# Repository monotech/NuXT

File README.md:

Based on schematics by Sergey Kiselev, with some small changes for combining optimization and board layout efficiency:

http://www.malinov.com/Home/sergeys-projects/isa-fdc-and-uart

http://www.malinov.com/Home/sergeys-projects/xt-cf-lite

http://www.malinov.com/Home/sergeys-projects/isa-supervga

https://github.com/skiselev/micro_8088

https://github.com/skiselev/isa8_backplane

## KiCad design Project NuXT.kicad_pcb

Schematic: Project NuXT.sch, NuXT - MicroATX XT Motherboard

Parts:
C1, C2, C3, C4, C5, C6, C9, C10, C12, C13, C15, C16, C17, C19, C31, C33, C36, C40, C46, C47, C48, C49, C50, C51, C52, C58, C59, C60, C63, C64, C65, C66, C67, C68, C70, C71, C72, C73, C74, C76, C77, C78, C85, C86: 100nF; C_Disc_D4.3mm_W1.9mm_P5.00mm
C8, C20, C21, C23, C24, C25, C26, C27, C28, C29, C30, C35, C56, C57, C61, C62, C69, C75, C79, C80, C81: 10uF; C_Disc_D4.3mm_W1.9mm_P5.00mm
C11, C38, C41, C42, C43, C44, C45, C54, C55, C87: 47pF; C_Disc_D4.3mm_W1.9mm_P5.00mm
C14: 5-30pF; C_Disc_D4.3mm_W1.9mm_P5.00mm
C18, C82, C83: 22pF; C_Disc_D4.3mm_W1.9mm_P5.00mm
C22: 10nF; C_Disc_D4.3mm_W1.9mm_P5.00mm
C34: 1uF; C_Disc_D4.3mm_W1.9mm_P5.00mm
C37: 100pF; C_Disc_D4.3mm_W1.9mm_P5.00mm
C39: 470pF; C_Disc_D4.3mm_W1.9mm_P5.00mm
C53: 1nF; C_Disc_D4.3mm_W1.9mm_P5.00mm
C84: 4.7nF; C_Disc_D4.3mm_W1.9mm_P5.00mm
D1, D4, D5: 1N4148; D_DO-34_SOD68_P7.62mm_Horizontal
D3: Bus Activity; LED_D3.0mm
D6: CF Activity; LED_D3.0mm
D7: 5VSB; LED_D3.0mm
D8: +5V; LED_D3.0mm
D9: +12V; LED_D3.0mm
D10: -12V; LED_D3.0mm
D11: -5V; LED_D3.0mm
F1: 1.1A; C_Disc_D4.3mm_W1.9mm_P5.00mm
FB1, FB2, FB3, FB4, FB5, FB6: BEAD; R_Axial_DIN0204_L3.6mm_D1.6mm_P7.62mm_Horizontal
HOLE1, HOLE2, HOLE3, HOLE4, HOLE5, HOLE6: HOLE; MountingHole_4mm_Pad_Via
ISA1, ISA2, ISA3, ISA4: BUSPC_HOST; Conn_Edge_ISA8_Longpads
JP1: UART Config; PinHeader_2x08_P2.54mm_Vertical
L1: 2.7uH; R_Axial_DIN0207_L6.3mm_D2.5mm_P7.62mm_Horizontal
L2, L3: 5.7uH; R_Axial_DIN0207_L6.3mm_D2.5mm_P7.62mm_Horizontal
LOGO1: SYM_Arrow45_Large; Monotech Logo 18mm
LOGO2: SYM_Arrow45_Large; Monotech Logo 92mm
P1: Front Panel; PinHeader_2x05_P2.54mm_Horizontal
P2: Speaker; PinHeader_1x04_P2.54mm_Horizontal
P3: ATX Power; Molex_Mini-Fit_Jr_5569-20A2_2x10_P4.20mm_Horizontal
P4: Floppy; Pin_Header_Straight_2x17_Pitch2.54mm_shrouded
P5: PS/2 Keyboard; Conn_Mini_DIN_6pin
P6: Serial Port; Conn_Dsub_DE9M
P7: VGA Port; DSUB-15-HD_Female_Horizontal_CONNFLY_DS1308
P8: CF_CARD; CF_Slot_3M_N7E50-7516TS0884
Q1: PN2222 EBC; TO-92L_Inline_Wide
R1, R15: 470; R_Axial_DIN0207_L6.3mm_D2.5mm_P7.62mm_Horizontal
R2, R33: 1M; R_Axial_DIN0207_L6.3mm_D2.5mm_P7.62mm_Horizontal
R3, R11, R14, R16, R31: 10K; R_Axial_DIN0207_L6.3mm_D2.5mm_P7.62mm_Horizontal
R4, R5: 47; R_Axial_DIN0207_L6.3mm_D2.5mm_P7.62mm_Horizontal
R6, R7, R8, R12, R13, R18, R29, R30: 1K; R_Axial_DIN0207_L6.3mm_D2.5mm_P7.62mm_Horizontal
R9, R21, R22: 33; R_Axial_DIN0207_L6.3mm_D2.5mm_P7.62mm_Horizontal
R10, R20, R26, R27: 4.7K; R_Axial_DIN0207_L6.3mm_D2.5mm_P7.62mm_Horizontal
R17: 100; R_Axial_DIN0207_L6.3mm_D2.5mm_P7.62mm_Horizontal
R19, R23, R24, R25: 150; R_Axial_DIN0207_L6.3mm_D2.5mm_P7.62mm_Horizontal
R28: 5.6K; R_Axial_DIN0207_L6.3mm_D2.5mm_P7.62mm_Horizontal
R32: 1.5K; R_Axial_DIN0207_L6.3mm_D2.5mm_P7.62mm_Horizontal
RN1: 4.7K; R_Array_SIP9
RN2, RN3, RN6, RN14, RN15: 10K; R_Array_SIP9
RN4, RN5, RN12: 4.7K; R_Array_SIP7
RN13: 1K; R_Array_SIP7
SP1: Speaker; MagneticBuzzer_ProSignal_ABT-410-RC
SW1: System Config; SW_DIP_SPSTx10_Slide_9.78x27.58mm_W7.62mm_P2.54mm
SW2: UMB Config; SW_DIP_SPSTx05_Slide_9.78x14.88mm_W7.62mm_P2.54mm
SW3: ROM Socket Address; SW_DIP_SPSTx04_Slide_9.78x12.34mm_W7.62mm_P2.54mm
SW4: U35 ROM Size; SW_MS-22D18G2
SW5: Power; SW_PUSH_6mm
SW6: Reset; SW_PUSH_6mm
U1: 8088; DIP-40_W15.24mm_Socket
U2: 8087; DIP-40_W15.24mm_Socket
U3: SST39SF010A; DIP-32_W15.24mm_Socket
U4, U5: AS6C4008; SSOP-32_11.305x20.495mm_P1.27mm
U6: FE2010A; PLCC-84_THT-Socket
U7: ATF16V8B; DIP-20_W7.62mm_Socket
U9: PIC12F629; DIP-8_W7.62mm_Socket
U10, U11, U12: 74F573; DIP-20_W7.62mm
U13, U14: 74F245; DIP-20_W7.62mm
U15, U16: 74F244; DIP-20_W7.62mm
U17: 74LS14; DIP-14_W7.62mm
U18: 74LS74; DIP-14_W7.62mm
U19: 7905; TO220-3_Soldertab
U20: TVGA9000i; PQFP-160_28x28mm_P0.65mm_LongPads
U21: 27C256; DIP-28_W15.24mm_Socket
U22, U23, U24, U25: 256Kx4 70ns; DIP-20_W7.62mm_Socket
U26, U36: 74LS688; DIP-20_W7.62mm
U27: 74LS32; DIP-14_W7.62mm
U28: 74LS04; DIP-14_W7.62mm
U29: 82077AA/PC8477; PLCC-68_THT-Socket
U30: 16(C)x50; PLCC-44_THT-Socket
U31: GD75232/75(C)185; DIP-20_W7.62mm
U32, U33: 74LS138; DIP-16_W7.62mm
U35: 28C64B/28C256; DIP-28_W15.24mm_Socket
X1: 28.63636MHz; Crystal_HC49-4H_Vertical
X2: 40MHz; Crystal_HC49-4H_Vertical
X3: 1.8432MHz TTL; Oscillator_DIP-14
X4: 24MHz; Crystal_HC49-4H_Vertical
X5: 1.8432MHz; Crystal_HC49-U_Horizontal_Solderpad

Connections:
/0x2E8: JP1.9, U32.11 (~Y4)
/0x2F8: JP1.13, U32.9 (~Y6)
/0x3E8: JP1.11, U32.10 (~Y5)
/0x3F0: SW1.16, U32.12 (~Y3)
/0x3F8: JP1.15, U32.7 (~Y7)
/5VSB: C29.1, C31.1, C33.1, D4.1 (K), D5.1 (K), D7.2 (A), P3.9 (5VSB), R14.1, R16.1, U17.9, U17.11, U17.13, U17.14 (VCC), U18.1 (~R), U18.10 (~S), U18.13 (~R), U18.14 (VCC)
/12V: C30.1, C73.1, C75.1, D9.2 (A), ISA1.9 (+12V), ISA2.9 (+12V), ISA3.9 (+12V), ISA4.9 (+12V), P3.10 (12V), U31.1 (VDD)
/-5V: C28.2, D11.1 (K), ISA1.5 (-5V), ISA2.5 (-5V), ISA3.5 (-5V), ISA4.5 (-5V), U19.3 (OUT)
/-12V: C24.2, C78.2, C79.2, D10.1 (K), ISA1.7 (-12V), ISA2.7 (-12V), ISA3.7 (-12V), ISA4.7 (-12V), P3.12 (-12V), U19.2 (IN), U31.10 (VSS)
/A0: ISA1.62 (SA0), ISA2.62 (SA0), ISA3.62 (SA0), ISA4.62 (SA0), U3.12 (A0), U4.12 (A0), U5.12 (A0), U10.19 (O0), U20.135 (SA0), U29.7 (A0), U30.31 (A0), U35.10 (A0)
/A1: ISA1.61 (SA1), ISA2.61 (SA1), ISA3.61 (SA1), ISA4.61 (SA1), P8.20 (A0), U3.11 (A1), U4.11 (A1), U5.11 (A1), U10.18 (O1), U20.136 (SA1), U21.10 (A0), U29.8 (A1), U30.30 (A1), U35.9 (A1)
/A2: ISA1.60 (SA2), ISA2.60 (SA2), ISA3.60 (SA2), ISA4.60 (SA2), P8.19 (A1), U3.10 (A2), U4.10 (A2), U5.10 (A2), U10.17 (O2), U20.137 (SA2), U21.9 (A1), U29.10 (A2), U30.29 (A2), U35.8 (A2)
/A3: ISA1.59 (SA3), ISA2.59 (SA3), ISA3.59 (SA3), ISA4.59 (SA3), P8.18 (A2), U3.9 (A3), U4.9 (A3), U5.9 (A3), U10.16 (O3), U20.138 (SA3), U21.8 (A2), U32.3 (C), U35.7 (A3)
/A4: ISA1.58 (SA4), ISA2.58 (SA4), ISA3.58 (SA4), ISA4.58 (SA4), U3.8 (A4), U4.8 (A4), U5.8 (A4), U10.15 (O4), U20.139 (SA4), U21.7 (A3), U27.4, U28.1, U32.2 (B), U35.6 (A4)
/A5: ISA1.57 (SA5), ISA2.57 (SA5), ISA3.57 (SA5), ISA4.57 (SA5), U3.7 (A5), U4.7 (A5), U5.7 (A5), U10.14 (O5), U20.140 (SA5), U21.6 (A4), U26.2 (P0), U32.6 (G1), U35.5 (A5)
/A6: ISA1.56 (SA6), ISA2.56 (SA6), ISA3.56 (SA6), ISA4.56 (SA6), U3.6 (A6), U4.6 (A6), U5.6 (A6), U10.13 (O6), U20.141 (SA6), U21.5 (A5), U26.4 (P1), U33.1 (A), U35.4 (A6)
/A7: ISA1.55 (SA7), ISA2.55 (SA7), ISA3.55 (SA7), ISA4.55 (SA7), R12.1, U3.5 (A7), U4.5 (A7), U5.5 (A7), U10.12 (O7), U20.142 (SA7), U21.4 (A6), U26.6 (P2), U33.2 (B), U35.3 (A7)
/A8: ISA1.54 (SA8), ISA2.54 (SA8), ISA3.54 (SA8), ISA4.54 (SA8), U3.27 (A8), U4.27 (A8), U5.27 (A8), U11.19 (O0), U20.144 (SA8), U21.3 (A7), U26.8 (P3), U32.1 (A), U35.25 (A8)
/A9: ISA1.53 (SA9), ISA2.53 (SA9), ISA3.53 (SA9), ISA4.53 (SA9), U3.26 (A9), U4.26 (A9), U5.26 (A9), U11.18 (O1), U20.145 (SA9), U21.25 (A8), U26.11 (P4), U33.3 (C), U35.24 (A9)
/A10: ISA1.52 (SA10), ISA2.52 (SA10), ISA3.52 (SA10), ISA4.52 (SA10), U3.23 (A10), U4.23 (A10), U5.23 (A10), U11.17 (O2), U20.146 (SA10), U21.24 (A9), U35.21 (A10)
/A11: ISA1.51 (SA11), ISA2.51 (SA11), ISA3.51 (SA11), ISA4.51 (SA11), U3.25 (A11), U4.25 (A11), U5.25 (A11), U11.16 (O3), U20.147 (SA11), U21.21 (A10), U35.23 (A11)
/A12: ISA1.50 (SA12), ISA2.50 (SA12), ISA3.50 (SA12), ISA4.50 (SA12), U3.4 (A12), U4.4 (A12), U5.4 (A12), U11.15 (O4), U20.148 (SA12), U21.23 (A11), U35.2 (A12)
/A13: ISA1.49 (SA13), ISA2.49 (SA13), ISA3.49 (SA13), ISA4.49 (SA13), SW4.5 (B), U3.28 (A13), U4.28 (A13), U5.28 (A13), U11.14 (O5), U20.149 (SA13), U21.2 (A12), U35.26 (A13)
/A14: ISA1.48 (SA14), ISA2.48 (SA14), ISA3.48 (SA14), ISA4.48 (SA14), SW4.2 (B), U3.29 (A14), U4.3 (A14), U5.3 (A14), U11.13 (O6), U20.150 (SA14), U21.26 (A13), U35.1 (A14)
/A15: ISA1.47 (SA15), ISA2.47 (SA15), ISA3.47 (SA15), ISA4.47 (SA15), U3.3 (A15), U4.31 (A15), U5.31 (A15), U7.9 (I8), U11.12 (O7), U20.151 (SA15), U36.5 (R1)
/A16: ISA1.46 (SA16), ISA2.46 (SA16), ISA3.46 (SA16), ISA4.46 (SA16), U4.2 (A16), U5.2 (A16), U7.5 (I4), U12.15 (O4), U20.152 (SA16), U36.3 (R0)
/A17: ISA1.45 (SA17), ISA2.45 (SA17), ISA3.45 (SA17), ISA4.45 (SA17), U4.30 (A17), U5.30 (A17), U7.6 (I5), U12.14 (O5), U20.113 (SA17(LA17)), U36.14 (R5)
/A18: ISA1.44 (SA18), ISA2.44 (SA18), ISA3.44 (SA18), ISA4.44 (SA18), U4.1 (A18), U5.1 (A18), U7.7 (I6), U12.13 (O6), U20.114 (SA18(LA18)), U36.16 (R6)
/A19: ISA1.43 (SA19), ISA2.43 (SA19), ISA3.43 (SA19), ISA4.43 (SA19), U4.22 (~CE), U7.8 (I7), U12.12 (O7), U20.115 (SA19(LA19)), U36.18 (R7)
/AA8: U1.8 (A8), U2.8 (AD8), U6.44 (A8), U11.2 (D0)
/AA9: U1.7 (A9), U2.7 (AD9), U6.45 (A9), U11.3 (D1)
/AA10: U1.6 (A10), U2.6 (AD10), U6.46 (A10), U11.4 (D2)
/AA11: U1.5 (A11), U2.5 (AD11), U6.47 (A11), U11.5 (D3)
/AA12: U1.4 (A12), U2.4 (AD12), U6.48 (A12), U11.6 (D4)
/AA13: U1.3 (A13), U2.3 (AD13), U6.49 (A13), U11.7 (D5)
/AA14: U1.2 (A14), U2.2 (AD14), U6.50 (A14), U11.8 (D6)
/AA15: U1.39 (A15), U2.39 (AD15), U6.51 (A15), U11.9 (D7)
/AA16: U1.38 (A16/S3), U2.38 (A16/S3), U6.52 (A16), U12.6 (D4)
/AA17: U1.37 (A17/S4), U2.37 (A17/S4), U6.53 (A17), U12.7 (D5)
/AA18: U1.36 (A18/S5), U2.36 (A18/S5), U6.54 (A18), U12.8 (D6)
/AA19: U1.35 (A19/S6), U2.35 (A19/S6), U6.55 (A19), U12.9 (D7)
/AD0: U1.16 (AD0), U2.16 (AD0), U3.13 (DQ0), U6.34 (AD0), U10.2 (D0), U13.2 (A1)
/AD1: U1.15 (AD1), U2.15 (AD1), U3.14 (DQ1), U6.35 (AD1), U10.3 (D1), U13.3 (A2)
/AD2: U1.14 (AD2), U2.14 (AD2), U3.15 (DQ2), U6.36 (AD2), U10.4 (D2), U13.4 (A3)
/AD3: U1.13 (AD3), U2.13 (AD3), U3.17 (DQ3), U6.37 (AD3), U10.5 (D3), U13.5 (A4)
/AD4: U1.12 (AD4), U2.12 (AD4), U3.18 (DQ4), U6.38 (AD4), U10.6 (D4), U13.6 (A5)
/AD5: U1.11 (AD5), U2.11 (AD5), U3.19 (DQ5), U6.39 (AD5), U10.7 (D5), U13.7 (A6)
/AD6: U1.10 (AD6), U2.10 (AD6), U3.20 (DQ6), U6.40 (AD6), U10.8 (D6), U13.8 (A7)
/AD7: U1.9 (AD7), U2.9 (AD7), U3.21 (DQ7), U6.41 (AD7), U10.9 (D7), U13.9 (A8)
/AEN: ISA1.42 (AEN), ISA2.42 (AEN), ISA3.42 (AEN), ISA4.42 (AEN), SW1.12, SW1.15, U16.16 (Y2), U20.22 (AEN), U32.4 (~G2A)
/ALE: ISA1.28 (ALE), ISA2.28 (ALE), ISA3.28 (ALE), ISA4.28 (ALE), U15.3 (Y4)
/APNMI: U2.32 (INT), U6.29 (APNMI)
/AT_KBCLK: D1.2 (A), P5.5, RN5.3 (R2), U9.5 (GP2/T0CKI/INT/COUT)
/AT_KBDATA: P5.1, RN5.2 (R1), U9.6 (GP1/CIN-/ICSPCLK)
/AVDD1: C40.1, C56.1, C59.1, L2.2, U20.124 (AVDD1)
/AVDD2: C57.1, C60.1, L3.2, U20.6 (AVDD2), U20.13 (AVDD2)
/B: FB3.1, R25.1, U20.2 (B)
/BLUE: C45.1, FB3.2, P7.3
/CF_DMARQ: P8.43 (~INPACK), R28.1
/CF_IORDY: P8.42 (IORDY), R30.1
/CLK: ISA1.20 (CLK), ISA2.20 (CLK), ISA3.20 (CLK), ISA4.20 (CLK), R5.1
/CLK88: U1.19 (CLK), U2.19 (CLK), U6.19 (CLOCK), U15.8 (A4)
/CS_RomSocket: U35.20 (CS), U36.19 (P=R)
/CTS: P6.8, U31.7 (RA4)
/D0: ISA1.40 (SD0), ISA2.40 (SD0), ISA3.40 (SD0), ISA4.40 (SD0), P8.21 (D0), RN2.2 (R1), U13.18 (B1), U14.2 (A1), U20.25 (SD0), U29.11 (DB0), U30.2 (D0), U35.11 (D0)
/D1: ISA1.39 (SD1), ISA2.39 (SD1), ISA3.39 (SD1), ISA4.39 (SD1), P8.22 (D1), RN2.3 (R2), U13.17 (B2), U14.3 (A2), U20.26 (SD1), U29.13 (DB1), U30.3 (D1), U35.12 (D1)
/D2: ISA1.38 (SD2), ISA2.38 (SD2), ISA3.38 (SD2), ISA4.38 (SD2), P8.23 (D2), RN2.4 (R3), U13.16 (B3), U14.4 (A3), U20.27 (SD2), U29.14 (DB2), U30.4 (D2), U35.13 (D2)
/D3: ISA1.37 (SD3), ISA2.37 (SD3), ISA3.37 (SD3), ISA4.37 (SD3), P8.2 (D3), RN2.5 (R4), U13.15 (B4), U14.5 (A4), U20.28 (SD3), U29.15 (DB3), U30.5 (D3), U35.15 (D3)
/D4: ISA1.36 (SD4), ISA2.36 (SD4), ISA3.36 (SD4), ISA4.36 (SD4), P8.3 (D4), RN2.6 (R5), U13.14 (B5), U14.6 (A5), U20.29 (SD4), U29.17 (DB4), U30.6 (D4), U35.16 (D4)
/D5: ISA1.35 (SD5), ISA2.35 (SD5), ISA3.35 (SD5), ISA4.35 (SD5), P8.4 (D5), RN2.7 (R6), U13.13 (B6), U14.7 (A6), U20.30 (SD5), U29.19 (DB5), U30.7 (D5), U35.17 (D5)
/D6: ISA1.34 (SD6), ISA2.34 (SD6), ISA3.34 (SD6), ISA4.34 (SD6), P8.5 (D6), RN2.8 (R7), U13.12 (B7), U14.8 (A7), U20.31 (SD6), U29.20 (DB6), U30.8 (D6), U35.18 (D6)
/D7: ISA1.33 (SD7), ISA2.33 (SD7), ISA3.33 (SD7), ISA4.33 (SD7), P8.6 (D7), RN2.9 (R8), U13.11 (B8), U14.9 (A8), U20.32 (SD7), U29.22 (DB7), U30.9 (D7), U35.19 (D7)
/DCD: P6.1, U31.2 (RA1)
/DENSL: P4.2, U29.49 (DENSEL)
/DIR: U6.72 (DTR), U13.1 (DIR)
/DRQ1: ISA1.18 (DRQ1), ISA2.18 (DRQ1), ISA3.18 (DRQ1), ISA4.18 (DRQ1), U6.58 (DRQ1)
/DRQ2: ISA1.6 (DRQ2), ISA2.6 (DRQ2), ISA3.6 (DRQ2), ISA4.6 (DRQ2), U6.57 (DRQ2), U29.24 (DRQ)
/DRQ3: ISA1.16 (DRQ3), ISA2.16 (DRQ3), ISA3.16 (DRQ3), ISA4.16 (DRQ3), U6.56 (DRQ3)
/DSA: P4.14, U29.58 (DS0)
/DSB: P4.12, U29.62 (DS1)
/DSKCG: P4.34, RN13.6 (R5), U29.31 (DSKCHG)
/DSR: P6.6, U31.3 (RA2)
/DTR: P6.4, U31.8 (DY3)
/E0_PASS: RN15.4 (R3), SW1.3, U9.4 (GP3/~MCLR~/Vpp)
/EN_RomSocket: RN6.2 (R1), SW1.9, U36.1 (G)
/EOP: U6.59 (EOP), U15.4 (A2)
/FloppyDIR: P4.18, U29.56 (DIR)
/G: FB2.1, R24.1, U20.3 (G)
/GREEN: C44.1, FB2.2, P7.2
/HDD_LED_Ext: P1.3, U28.10
/HDSEL: P4.32, U29.51 (HDSEL)
/HSYNC: FB5.2, U20.48 (HSYNC)
/INDEX: P4.8, RN13.2 (R1), U29.26 (INDX)
/INT: U1.18 (INTR), U6.10 (INT)
/IORDY: ISA1.41 (IO_READY), ISA2.41 (IO_READY), ISA3.41 (IO_READY), ISA4.41 (IO_READY), U6.28 (IORDY), U20.157 (IOCHRDY)
/IRQ2: ISA1.4 (IRQ2), ISA2.4 (IRQ2), ISA3.4 (IRQ2), ISA4.4 (IRQ2), U6.76 (IRQ2)
/IRQ3: ISA1.25 (IRQ3), ISA2.25 (IRQ3), ISA3.25 (IRQ3), ISA4.25 (IRQ3), JP1.1, U6.77 (IRQ3)
/IRQ4: ISA1.24 (IRQ4), ISA2.24 (IRQ4), ISA3.24 (IRQ4), ISA4.24 (IRQ4), JP1.3, U6.78 (IRQ4)
/IRQ5: ISA1.23 (IRQ5), ISA2.23 (IRQ5), ISA3.23 (IRQ5), ISA4.23 (IRQ5), JP1.5, U6.79 (IRQ5)
/IRQ6: ISA1.22 (IRQ6), ISA2.22 (IRQ6), ISA3.22 (IRQ6), ISA4.22 (IRQ6), U6.80 (IRQ6), U29.23 (INT)
/IRQ7: ISA1.21 (IRQ7), ISA2.21 (IRQ7), ISA3.21 (IRQ7), ISA4.21 (IRQ7), JP1.7, U6.81 (IRQ7)
/KBCLK: RN5.4 (R3), U6.25 (KBCLK), U9.2 (GP5/T1CKI/OSC1/CLKIN)
/KBDATA: RN5.5 (R4), U6.26 (KBDA), U9.3 (GP4/~T1G~/OSC2/CLKOUT)
/KBD_VCC: F1.1, P5.4
/LE: U6.70 (ALE), U10.11 (LE), U11.11 (LE), U12.11 (LE)
/MAA0: U20.52 (MAA0), U22.6 (A0), U24.6 (A0)
/MAA1: U20.53 (MAA1), U22.7 (A1), U24.7 (A1)
/MAA2: U20.54 (MAA2), U22.8 (A2), U24.8 (A2)
/MAA3: U20.55 (MAA3), U22.9 (A3), U24.9 (A3)
/MAA4: U20.56 (MAA4), U22.11 (A4), U24.11 (A4)
/MAA5: U20.57 (MAA5), U22.12 (A5), U24.12 (A5)
/MAA6: U20.59 (MAA6), U22.13 (A6), U24.13 (A6)
/MAA7: U20.60 (MAA7), U22.14 (A7), U24.14 (A7)
/MAA8: U20.61 (MAA8), U22.15 (A8), U24.15 (A8)
/MAB0: U20.73 (MAB0), U23.6 (A0), U25.6 (A0)
/MAB1: U20.74 (MAB1), U23.7 (A1), U25.7 (A1)
/MAB2: U20.75 (MAB2), U23.8 (A2), U25.8 (A2)
/MAB3: U20.76 (MAB3), U23.9 (A3), U25.9 (A3)
/MAB4: U20.77 (MAB4), U23.11 (A4), U25.11 (A4)
/MAB5: U20.78 (MAB5), U23.12 (A5), U25.12 (A5)
/MAB6: U20.82 (MAB6), U23.13 (A6), U25.13 (A6)
/MAB7: U20.83 (MAB7), U23.14 (A7), U25.14 (A7)
/MAB8: U20.84 (MAB8), U23.15 (A8), U25.15 (A8)
/MD0: U4.13 (DQ0), U5.13 (DQ0), U14.18 (B1)
/MD1: U4.14 (DQ1), U5.14 (DQ1), U14.17 (B2)
/MD2: U4.15 (DQ2), U5.15 (DQ2), U14.16 (B3)
/MD3: U4.17 (DQ3), U5.17 (DQ3), U14.15 (B4)
/MD4: U4.18 (DQ4), U5.18 (DQ4), U14.14 (B5)
/MD5: U4.19 (DQ5), U5.19 (DQ5), U14.13 (B6)
/MD6: U4.20 (DQ6), U5.20 (DQ6), U14.12 (B7)
/MD7: U4.21 (DQ7), U5.21 (DQ7), U14.11 (B8)
/MEA: P4.10, U29.57 (ME0)
/MEB: P4.16, U29.61 (ME1)
/MONITOR: FB4.2, R26.1, U20.46 (MONITOR)
/NMI: U1.17 (NMI), U6.31 (NMI)
/OSC: U6.20 (OSC), U15.2 (A1)
/OSCDRV: ISA1.30 (OSC), ISA2.30 (OSC), ISA3.30 (OSC), ISA4.30 (OSC), R4.1, U20.98 (ROMCLK)
/PWR_SW: P1.6, R14.2, R15.2, SW5.2
/QS0: U1.25 (QS0), U2.25 (QS0)
/QS1: U1.24 (QS1), U2.24 (QS1)
/R: FB1.1, R23.1, U20.4 (R)
/RDATA: P4.30, RN13.5 (R4), U29.41 (RDDATA)
/READY: U1.22 (READY), U2.22 (READY), U6.17 (READY)
/RED: C43.1, FB1.2, P7.1
/RESET: U1.21 (RESET), U2.21 (RESET), U6.18 (RESET), U16.2 (A1)
/RI: P6.9, U31.9 (RA5)
/RMD0: U20.43 (RMD0), U21.11 (DQ0)
/RMD1: SW1.14, U20.39 (RMD1), U21.12 (DQ1)
/RMD2: U20.38 (RMD2), U21.13 (DQ2)
/RMD3: U20.37 (RMD3), U21.15 (DQ3)
/RMD4: RN12.3 (R2), U20.36 (RMD4), U21.16 (DQ4)
/RMD5: U20.35 (RMD5), U21.17 (DQ5)
/RMD6: RN12.2 (R1), U20.34 (RMD6), U21.18 (DQ6)
/RMD7: U20.33 (RMD7), U21.19 (DQ7)
/ROMA0: U20.97 (ROMBA0), U21.27 (A14)
/ROM_A16: R3.2, SW1.4, U3.2 (A16)
/RSTDRV: ISA1.2 (RESET), ISA2.2 (RESET), ISA3.2 (RESET), ISA4.2 (RESET), R18.1, U16.18 (Y1), U28.3, U29.32 (RESET), U30.39 (MR)
/RTS: P6.7, U31.5 (DY1)
/RX: P6.2, U31.4 (RA3)
/SIN: U30.11 (SIN), U31.17 (RY3)
/SOUT: U30.13 (SOUT), U31.15 (DA2)
/SPKR: U6.14 (SPEAKR), U7.14 (I/O6)
/STEP: P4.20, U29.55 (STEP)
/TC: ISA1.27 (TC), ISA2.27 (TC), ISA3.27 (TC), ISA4.27 (TC), U15.16 (Y2), U29.25 (TC)
/TRK00: P4.26, RN13.3 (R2), U29.2 (TRK0)
/TX: P6.3, U31.6 (DY2)
/UART_IRQ: JP1.2, JP1.4, JP1.6, JP1.8, U30.33 (INTR)
/VMD0: U20.64 (MD0), U22.1 (DQ1)
/VMD1: U20.65 (MD1), U22.2 (DQ2)
/VMD2: SW1.13, U20.66 (MD2), U22.18 (DQ3)
/VMD3: RN12.4 (R3), U20.67 (MD3), U22.19 (DQ4)
/VMD4: U20.68 (MD4), U24.1 (DQ1)
/VMD5: U20.70 (MD5), U24.2 (DQ2)
/VMD6: U20.71 (MD6), U24.18 (DQ3)
/VMD7: RN12.5 (R4), U20.72 (MD7), U24.19 (DQ4)
/VMD16: U20.89 (MD16), U23.1 (DQ1)
/VMD17: U20.90 (MD17), U23.2 (DQ2)
/VMD18: U20.91 (MD18), U23.18 (DQ3)
/VMD19: U20.92 (MD19), U23.19 (DQ4)
/VMD20: U20.93 (MD20), U25.1 (DQ1)
/VMD21: U20.94 (MD21), U25.2 (DQ2)
/VMD22: U20.95 (MD22), U25.18 (DQ3)
/VMD23: U20.96 (MD23), U25.19 (DQ4)
/VSYNC: FB6.2, U20.47 (VSYNC)
/WDATA: P4.22, U29.53 (WRDATA)
/WE: P4.24, U29.52 (WE)
/WE_RomSocket: RN15.7 (R6), SW1.10, U35.27 (WE)
/WP: P4.28, RN13.4 (R3), U29.1 (WP)
/XAEN: U6.30 (AEN), U16.4 (A2)
/XALE: U6.69 (BALE), U15.17 (A4)
/XTCF_EN: RN15.6 (R5), SW1.6, U26.1 (~G)
/~0WS: ISA1.8 (UNUSED), ISA2.8 (UNUSED), ISA3.8 (UNUSED), ISA4.8 (UNUSED)
/~CAS: C42.1, R22.2, U22.17 (~CAS), U23.17 (~CAS), U24.17 (~CAS), U25.17 (~CAS)
/~CF_CS0: P8.7 (~CS0), U27.6
/~CF_CS1: P8.32 (~CS1), U27.3
/~CF_DASP: P8.45 (~DASP), U28.5
/~CF_RESET: P8.41 (~RESET), U28.4
/~CTS: U30.40 (~CTS), U31.14 (RY4)
/~DACK0: ISA1.19 (DACK0), ISA2.19 (DACK0), ISA3.19 (DACK0), ISA4.19 (DACK0), U15.14 (Y3), U20.158 (ENMEM)
/~DACK1: ISA1.17 (DACK1), ISA2.17 (DACK1), ISA3.17 (DACK1), ISA4.17 (DACK1), U16.12 (Y4)
/~DACK2: ISA1.26 (DACK2), ISA2.26 (DACK2), ISA3.26 (DACK2), ISA4.26 (DACK2), U15.5 (Y3), U29.3 (~DACK)
/~DACK3: ISA1.15 (DACK3), ISA2.15 (DACK3), ISA3.15 (DACK3), ISA4.15 (DACK3), U16.14 (Y3)
/~DCD: U30.42 (~DCD), U31.19 (RY1)
/~DEN: U6.71 (~DEN), U13.19 (~G)
/~DSR: U30.41 (~DSR), U31.18 (RY2)
/~DTR: U30.37 (~DTR), U31.13 (DA3)
/~EPSL: U6.6 (~EPSL)
/~FDC_CS: RN15.5 (R4), SW1.5, U29.6 (CS)
/~IOCHK: ISA1.32 (IO_CH_CK), ISA2.32 (IO_CH_CK), ISA3.32 (IO_CH_CK), ISA4.32 (IO_CH_CK), U6.27 (~IOCHK), U20.24 (~NMI)
/~IOR: ISA1.14 (IOR), ISA2.14 (IOR), ISA3.14 (IOR), ISA4.14 (IOR), P8.34 (~IORD), RN4.5 (R4), U16.9 (Y1), U20.153 (~IOR), U29.4 (~RD), U30.24 (~RD)
/~IOW: ISA1.13 (IOW), ISA2.13 (IOW), ISA3.13 (IOW), ISA4.13 (IOW), P8.35 (~IOWR), R17.1, RN4.4 (R3), U16.7 (Y2), U29.5 (~WR), U30.20 (~WR)
/~MEMR: C38.1, ISA1.12 (MEMR), ISA2.12 (MEMR), ISA3.12 (MEMR), ISA4.12 (MEMR), RN4.3 (R2), U3.24 (~OE), U4.24 (~OE), U5.24 (~OE), U14.1 (DIR), U16.5 (Y3), U20.155 (~MEMR), U35.22 (OE)
/~MEMW: ISA1.11 (MEMW), ISA2.11 (MEMW), ISA3.11 (MEMW), ISA4.11 (MEMW), RN4.2 (R1), SW1.11, U3.31 (~WE), U4.29 (~WE), U5.29 (~WE), U16.3 (Y4), U20.156 (~MEMW)
/~PS_ON: P3.14 (~PS_ON), U18.5 (Q)
/~RAMCS: U6.5 (~RAMCS)
/~RAMCS2: U5.22 (~CE), U7.13 (I/O7)
/~RAMENA: U7.16 (I/O4), U14.19 (~G)
/~RAS: C41.1, R21.2, U22.4 (~RAS), U23.4 (~RAS), U24.4 (~RAS), U25.4 (~RAS)
/~RESIN: P1.7, R1.2, RN3.7 (R6), SW6.2
/~RI: U30.43 (~RI), U31.12 (RY5)
/~ROMCS: U3.22 (~CE), U7.12 (I/O8)
/~RQ/GT0: RN1.2 (R1), U1.31 (~RQ~/~GT0~), U6.24 (~RQ/GT)
/~RQ/GT1: RN1.4 (R3), U1.30 (~RQ~/~GT1~), U2.31 (~RQ~/~GT0~)
/~RQ/GT2: RN1.3 (R2), U2.33 (~RQ~/~GT1~)
/~RTS: U30.36 (~RTS), U31.16 (DA1)
/~S0: RN1.7 (R6), U1.26 (~S0), U2.26 (~S0), U6.75 (~S0)
/~S1: RN1.6 (R5), U1.27 (~S1), U2.27 (~S1), U6.74 (~S1)
/~S2: RN1.5 (R4), U1.28 (~S2), U2.28 (~S2), U6.73 (~S2)
/~SPKR: R7.2, U7.15 (I/O5)
/~TEST: RN1.8 (R7), U1.23 (~TEST), U2.23 (BUSY)
/~UART_CS: JP1.10, JP1.12, JP1.14, JP1.16, R31.2, U30.16 (~CS2)
/~VID0: RN15.2 (R1), SW1.1, U6.12 (VID0)
/~VID1: RN15.3 (R2), SW1.2, U6.13 (VID1)
/~VROMCS: U20.45 (~ROMCS), U21.22 (~OE)
/~WE0: U20.88 (~WE0), U22.3 (~WE), U24.3 (~WE)
/~WE2: U20.87 (~WE2), U23.3 (~WE), U25.3 (~WE)
/~XDACK0: U6.63 (~DACK0), U15.6 (A3)
/~XDACK1: U6.62 (~DACK1), U16.8 (A4)
/~XDACK2: U6.61 (~DACK2), U15.15 (A3)
/~XDACK3: U6.60 (~DACK3), U16.6 (A3)
/~XIOR: U6.65 (~IOR), U16.11 (A1)
/~XIOW: U6.66 (~IOW), U16.13 (A2)
/~XMEMR: U6.67 (~MEMR), U16.15 (A3)
/~XMEMW: U6.68 (~MEMW), U16.17 (A4)
GND: C1.2, C2.2, C3.2, C4.2, C5.2, C6.2, C8.2, C9.2, C10.2, C11.2, C12.2, C13.2, C15.2, C16.2, C17.2, C18.2, C19.2, C20.2, C21.2, C22.2, C23.2, C24.1, C25.2, C26.2, C27.2, C28.1, C29.2, C30.2, C31.2, C33.2, C34.2, C35.2, C36.2, C37.2, C38.2, C39.2, C41.2, C42.2, C43.2, C44.2, C45.2, C46.2, C47.2, C48.2, C49.2, C50.2, C51.2, C52.2, C53.2, C54.2, C55.2, C56.2, C57.2, C58.2, C59.2, C60.2, C61.2, C62.2, C63.2, C64.2, C65.2, C66.2, C67.2, C68.2, C69.2, C70.2, C71.2, C72.2, C73.2, C74.2, C75.2, C76.2, C77.2, C78.1, C79.1, C80.2, C81.2, C82.2, C83.2, C85.2, C86.2, C87.2, HOLE1.1, HOLE2.1, HOLE3.1, HOLE4.1, HOLE5.1, HOLE6.1, ISA1.1 (GND), ISA1.10 (GND), ISA1.31 (GND), ISA2.1 (GND), ISA2.10 (GND), ISA2.31 (GND), ISA3.1 (GND), ISA3.10 (GND), ISA3.31 (GND), ISA4.1 (GND), ISA4.10 (GND), ISA4.31 (GND), P1.4, P1.5, P1.8, P3.3 (GND), P3.5 (GND), P3.7 (GND), P3.13 (GND), P3.15 (GND), P3.16 (GND), P3.17 (GND), P4.1, P4.5, P4.7, P4.11, P4.13, P4.15, P4.19, P4.21, P4.23, P4.25, P4.29, P4.31, P5.3, P5.~, P6.5, P7.5, P7.6, P7.7, P7.8, P7.10, P8.1 (GND), P8.8 (A10), P8.9 (~ATASEL), P8.10 (A9), P8.11 (A8), P8.12 (A7), P8.14 (A6), P8.15 (A5), P8.16 (A4), P8.17 (A3), P8.39 (~CSEL), P8.50 (GND), Q1.1 (E), R3.1, R10.2, R11.1, R19.2, R23.2, R24.2, R25.2, R27.2, R28.2, RN6.1 (common), RN12.1 (common), RN14.1 (common), SW1.18, SW1.19, SW1.20, SW2.6, SW2.7, SW2.8, SW2.9, SW2.10, SW5.1, SW6.1, U1.1 (GND), U1.20 (GND), U1.33 (~MX), U2.1 (GND), U2.20 (GND), U3.16 (GND), U4.16 (GND), U5.16 (GND), U6.2 (GND), U6.11 (A64K), U6.16 (XSEL), U6.22 (GND), U6.32 (PTYIN), U6.42 (GND), U6.64 (GND), U7.10 (GND), U9.8 (GND), U10.1 (~OE), U10.10 (GND), U11.1 (~OE), U11.10 (GND), U12.1 (~OE), U12.2 (D0), U12.3 (D1), U12.4 (D2), U12.5 (D3), U12.10 (GND), U13.10 (GND), U14.10 (GND), U15.1 (~G), U15.10 (GND), U15.11 (A1), U15.13 (A2), U15.19 (~G), U16.1 (~G), U16.10 (GND), U16.19 (~G), U17.7 (GND), U18.7 (GND), U19.1 (GND), U20.1 (AVSS2), U20.7 (DVSS2), U20.23 (VSS), U20.41 (VSS), U20.42 (VSS), U20.49 (EVIDEO), U20.50 (ECLK), U20.58 (VSS), U20.79 (VSS), U20.80 (VSS), U20.101 (VSS), U20.121 (VSS), U20.122 (VSS), U20.126 (AVSS), U20.128 (DVSS1), U20.143 (VSS), U20.160 (VSS), U21.14 (GND), U21.20 (~CE), U22.16 (~OE), U22.20 (GND), U23.16 (~OE), U23.20 (GND), U24.16 (~OE), U24.20 (GND), U25.16 (~OE), U25.20 (GND), U26.3 (Q0), U26.5 (Q1), U26.7 (Q2), U26.10 (GND), U26.13 (P5), U26.14 (Q5), U26.15 (P6), U26.16 (Q6), U26.17 (P7), U26.18 (Q7), U27.7 (GND), U27.12, U27.13, U28.7 (GND), U29.9 (GND), U29.12 (GND), U29.16 (GND), U29.21 (GND), U29.30 (DRV2), U29.35 (~INVERT), U29.36 (GND), U29.45 (AVSS), U29.50 (GND), U29.54 (GND), U29.59 (GND), U29.65 (GND), U30.21 (WR), U30.22 (GND), U30.25 (RD), U30.28 (~ADS), U31.11 (GND), U32.8 (GND), U33.4 (~G2A), U33.5 (~G2B), U33.8 (GND), U35.14 (GND), U36.10 (GND), U36.11 (P4), U36.12 (R4), U36.13 (P5), X3.7 (GND)
unnamed: C8.1, R1.1, U6.15 (~REST)
unnamed: C11.1, R2.1, U6.23 (X1), X1.2
unnamed: C14.1, X1.1
unnamed: C14.2, R2.2, U6.21 (X2)
unnamed: C18.1, R33.2, U30.18 (XIN), X3.8 (OUT), X5.1
unnamed: C22.1, Q1.3 (C), R9.2
unnamed: C34.1, D4.2 (A), R15.1, U17.1
unnamed: C35.1, D5.2 (A), R16.2, U17.3
unnamed: C36.1, L1.1
unnamed: C37.1, R17.2, U20.154 (~IOW)
unnamed: C39.1, R18.2, U20.5 (RESET)
unnamed: C40.2, U20.125 (VLF)
unnamed: C53.1, FB4.1, P7.12
unnamed: C54.1, FB5.1, P7.13
unnamed: C55.1, FB6.1, P7.14
unnamed: C82.1, U29.33 (X1), X4.1
unnamed: C83.1, U29.34 (X2), X4.2
unnamed: C84.1, U29.38 (HIFIL)
unnamed: C84.2, U29.37 (LOFIL)
unnamed: C87.1, R32.1, R33.1, X5.2
unnamed: D1.1 (K), U9.7 (GP0/CIN+/ISCPDAT)
unnamed: D3.1 (K), R13.1
unnamed: D3.2 (A), U27.8, U28.13
unnamed: D6.1 (K), U28.8
unnamed: D6.2 (A), R29.1
unnamed: D7.1 (K), RN14.2 (R1)
unnamed: D8.1 (K), RN14.3 (R2)
unnamed: D9.1 (K), RN14.4 (R3)
unnamed: D10.2 (A), RN14.5 (R4)
unnamed: D11.2 (A), R11.2
unnamed: L1.2, U20.131 (XTL1), X2.2
unnamed: P1.1, R8.1
unnamed: P1.2, R6.1
unnamed: P2.1, R9.1
unnamed: P2.2, SP1.2
unnamed: P4.6, U29.28 (DRATE0)
unnamed: Q1.2 (B), R7.1
unnamed: R4.2, U15.18 (Y1)
unnamed: R5.2, U15.12 (Y4)
unnamed: R10.1, SW1.8
unnamed: R12.2, U18.11 (C)
unnamed: R13.2, U28.12
unnamed: R19.1, U20.18 (IRSET)
unnamed: R20.1, U20.102 (~MCS16)
unnamed: R21.1, U20.86 (~RAS)
unnamed: R22.1, U20.85 (~CAS)
unnamed: R27.1, SW1.7
unnamed: R32.2, U30.19 (XOUT)
unnamed: RN3.2 (R1), SW2.5, U7.2 (I1)
unnamed: RN3.3 (R2), SW2.4, U7.3 (I2)
unnamed: RN3.4 (R3), SW2.3, U7.4 (I3)
unnamed: RN3.5 (R4), SW2.2, U7.17 (I/O3)
unnamed: RN3.6 (R5), SW2.1, U7.18 (I/O2)
unnamed: RN6.3 (R2), SW3.8, U36.2 (P0)
unnamed: RN6.4 (R3), SW3.7, U36.4 (P1)
unnamed: RN6.5 (R4), SW3.6, U36.6 (P2)
unnamed: RN6.6 (R5), SW3.5, U36.8 (P3)
unnamed: RN6.7 (R6), SW4.1 (A), U36.7 (R2)
unnamed: RN6.8 (R7), SW4.4 (A), U36.9 (R3)
unnamed: U17.2, U18.3 (C)
unnamed: U17.4, U17.5
unnamed: U17.6, U18.4 (~S)
unnamed: U18.2 (D), U18.6 (~Q)
unnamed: U18.9 (Q), U27.9, U27.10
unnamed: U18.8 (~Q), U18.12 (D)
unnamed: U20.133 (XTL2), X2.1
unnamed: U26.19 (~P=Q), U27.2, U27.5
unnamed: U27.1, U28.2
unnamed: U28.6, U28.9, U28.11
unnamed: U30.10 (RCLK), U30.17 (~BAUDOUT)
unnamed: U32.5 (~G2B), U33.7 (~Y7)
VCC: C1.1, C2.1, C3.1, C4.1, C5.1, C6.1, C9.1, C10.1, C12.1, C13.1, C15.1, C16.1, C17.1, C19.1, C20.1, C21.1, C23.1, C25.1, C26.1, C27.1, C46.1, C47.1, C48.1, C49.1, C50.1, C51.1, C52.1, C58.1, C61.1, C62.1, C63.1, C64.1, C65.1, C66.1, C67.1, C68.1, C69.1, C70.1, C71.1, C72.1, C74.1, C76.1, C77.1, C80.1, C81.1, C85.1, C86.1, D8.2 (A), F1.2, ISA1.3 (VCC), ISA1.29 (VCC), ISA2.3 (VCC), ISA2.29 (VCC), ISA3.3 (VCC), ISA3.29 (VCC), ISA4.3 (VCC), ISA4.29 (VCC), L2.1, L3.1, P2.4, P3.4 (5V), P3.6 (5V), P3.19 (5V), P3.20 (5V), P8.13 (VCC), P8.36 (~WE), P8.38 (VCC), P8.44 (~REG), R6.2, R8.2, R20.2, R26.2, R29.2, R30.2, R31.1, RN1.1 (common), RN2.1 (common), RN3.1 (common), RN4.1 (common), RN5.1 (common), RN13.1 (common), RN15.1 (common), SP1.1, SW1.17, SW3.1, SW3.2, SW3.3, SW3.4, U1.40 (VCC), U2.34 (~BHE~/S7), U2.40 (VCC), U3.32 (VCC), U4.32 (VCC), U5.32 (VCC), U6.1 (VCC), U6.43 (VCC), U7.20 (VCC), U9.1 (VCC), U10.20 (VCC), U11.20 (VCC), U12.20 (VCC), U13.20 (VCC), U14.20 (VCC), U15.20 (VCC), U16.20 (VCC), U20.8 (DVDD2), U20.19 (VDD), U20.21 (ALE), U20.40 (VDD), U20.51 (ESYNC), U20.62 (VDD), U20.69 (VDD), U20.81 (VDD), U20.120 (VDD), U20.130 (DVDD1), U20.134 (VDD), U21.1 (VPP), U21.28 (VCC), U22.10 (VCC), U23.10 (VCC), U24.10 (VCC), U25.10 (VCC), U26.9 (Q3), U26.12 (Q4), U26.20 (VCC), U27.14 (VCC), U28.14 (VCC), U29.18 (VCC), U29.27 (IDENT), U29.39 (PLL0), U29.40 (VCC), U29.46 (AVCC), U29.60 (VCC), U29.68 (VCC), U30.14 (CS0), U30.15 (CS1), U30.44 (VCC), U31.20 (VCC), U32.16 (VCC), U33.6 (G1), U33.16 (VCC), U35.28 (VCC), U36.15 (P6), U36.17 (P7), U36.20 (VCC), X3.14 (VCC)

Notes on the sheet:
-5V Regulator
CPU Activity Indicator
ATX Power Connector
Mounting Holes
ATX Power On Circuit
Bypass Capacitors
ISA Bus Slots
Spare
SW2: UMB Config Default: All off 1: C0000-C7FFF 2: C8000-CFFFF 3: D0000-D7FFF 4: D8000-DFFFF 5: E0000-EFFFF
CPU Section
Spares
I/O Ports Chip Select Logic
Compact Flash Interface
XT-CF
VGA BIOS
SVGA
Fixed at 300h
Multi I/O
JP1: UART Config All open: Disabled 1: IRQ3 (COM2, COM4) 2: IRQ4 (COM1, COM3) 3: IRQ5 4: IRQ7 5: 2E8 (COM4) 6: 3E8 (COM3) 7: 2F8 (COM2) 8: 3F8 (COM1) Default: 2, 8 closed
Floppy DisK Controller
Serial Port Controller (UART)
C84 only needed for Intel FDC
NOTE: Only compatible with 28C64B 8K EEPROMs, not 28C64(non-B)
NOTE: ROM 0xC0000 - 0xDFFFF only
Boot ROM (Optional)
Remove pin 10 from header
SW1: System Config Default: 1, 2, 5, 6, 7 ON Video mode: 1 ON, 2 ON : VGA/EGA/None 1 ON, 2 OFF : 80x25 CGA 1 OFF, 2 ON : 40x25 CGA 1 OFF, 2 OFF: MDA/Hercules 3: Enable keyboard E0 scancode passthrough 4: Use 2nd half of system ROM instead of 1st half 5: Enable onboard primary floppy controller 6: E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
PSU Indicator LEDs
Optional DIP Oscillator instead of Crystal
Put serial circuitry close to bus

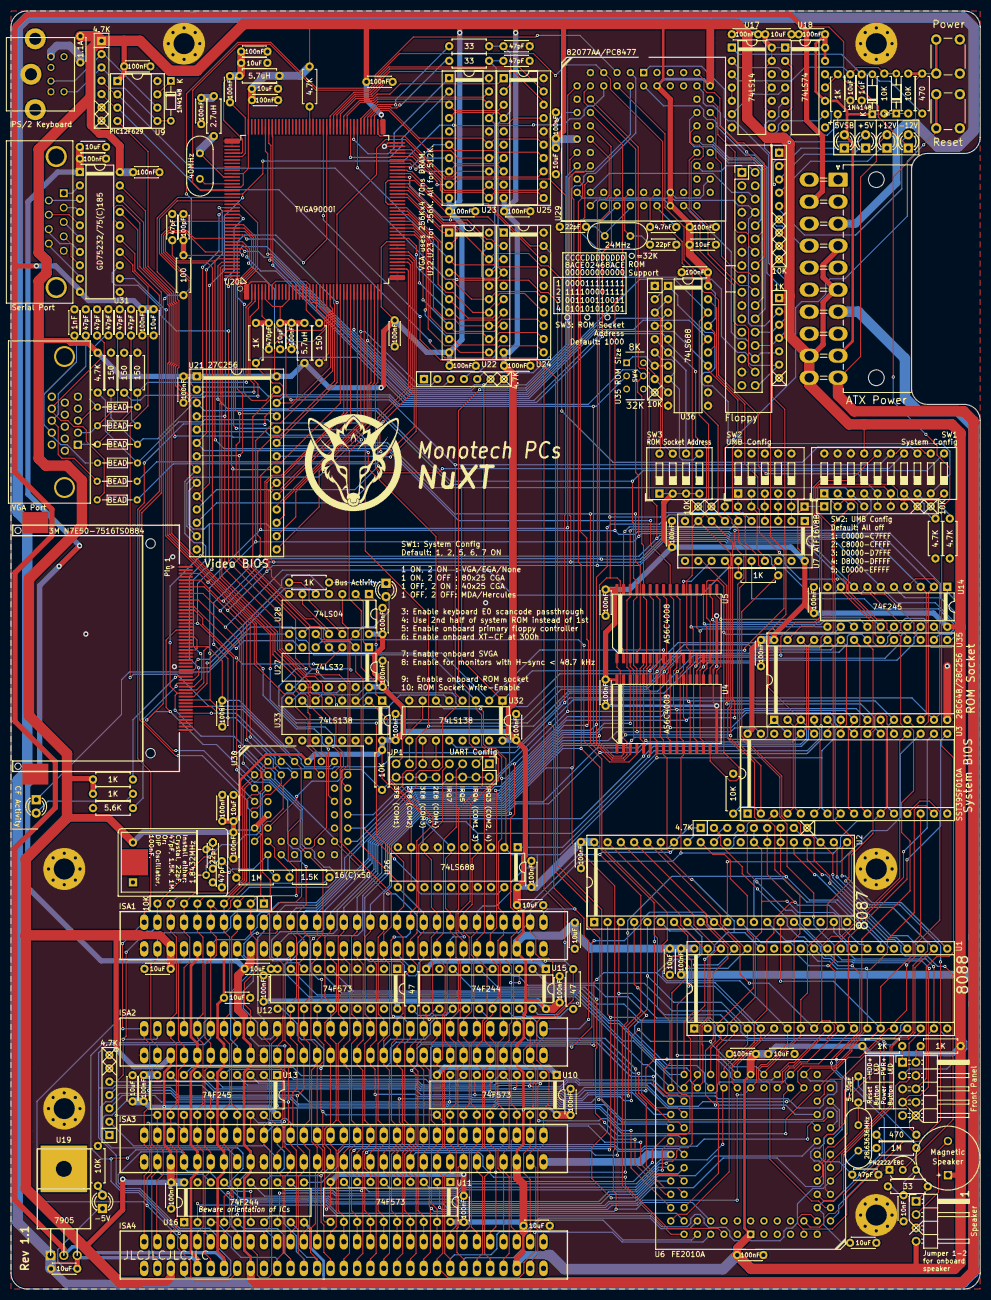
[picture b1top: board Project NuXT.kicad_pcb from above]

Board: 2 copper layers, 184.9 x 243.8 mm, 216 parts (1 on the bottom side), 315 nets.

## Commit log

2019-05-31 Rev 1.2
2019-07-06 Create test
2021-09-18 Update BIOS to 0.9.8 and XUB to R618
